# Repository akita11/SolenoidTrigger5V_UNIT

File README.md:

# SolenoidTrigger5V UNIT

5V電源のみで[タカハのスリムロック](https://www.takaha.co.jp/co/product-slim-lock/)など12V程度以上の高い電圧が必要な負荷を、コンデンサに蓄積したエネルギーで短時間駆動できるユニットです。駆動後は、繰り返しエネルギーを充電して駆動することができます。なおスリムロックの開閉状態をGrove端子から計測するための接続端子もあります。

## 使い方（接続方法）

オレンジの端子に、以下のように負荷を接続します。
- スリムロックのソレノイド（白ワイヤ）: 基板裏面"SOL"側（極性なし）
- スリムロックの開閉センサ（赤ワイヤ）: 基板裏面"ST"側（極性なし）

Grove端子にはM5Stack等のマイコンに接続します。

## 使い方（ソフトウエア）

Grove端子のp1（コネクタの端側）を駆動信号TRGを"1"にすると、コンデンサに蓄積したエネルギーでスリムロックなどの負荷を一瞬だけ駆動します（施錠状態のスリムロックが解錠されます）。
なお"1"にしてから負荷が駆動されるまでに0.5秒程度時間がかかります。充電動作中はオレンジLEDが点灯し、その間は負荷の駆動が行われません。

Grove端子のp2（コネクタのVDD側）は、ST端子がショート時には"0"、オープン時には"1"となり、Grove端子に接続したM5Stack等のマイコンから読み取ることができます。（内部プルアップ）

### UIFlow(v1)用のカスタムブロック

UIFlow(v1)で、Customから"SolenoidTrigger5V.m5b"を読み込むと、"SolenoidTrigger5VUnit"内の3つのブロックが使えるようになります。（上図はこれを読み込んだあと、"SolenoidTrgger5VUNIT_test_Core2.m5f"を読み込んだ例）

- Init : 解除信号(Groveのp1端子:CtrlPin)とST端子状態(Groveのp2端子:StatusPin)のピン番号を指定します。最初に1回だけ実行します。例：Core2のPortAはp1=GPIO33、p2=GPIO32なので、この図のように指定します。その他の機種・ポートのピン番号は仕様を確認してください。
- Unlock : ロック解除を行います
- Status : ST端子の状態を取得します。スリムロックの場合は、解錠時に"1"、施錠時に"0"になります。

## Author

Junichi Akita (@akita11) / akita@ifdl.jp

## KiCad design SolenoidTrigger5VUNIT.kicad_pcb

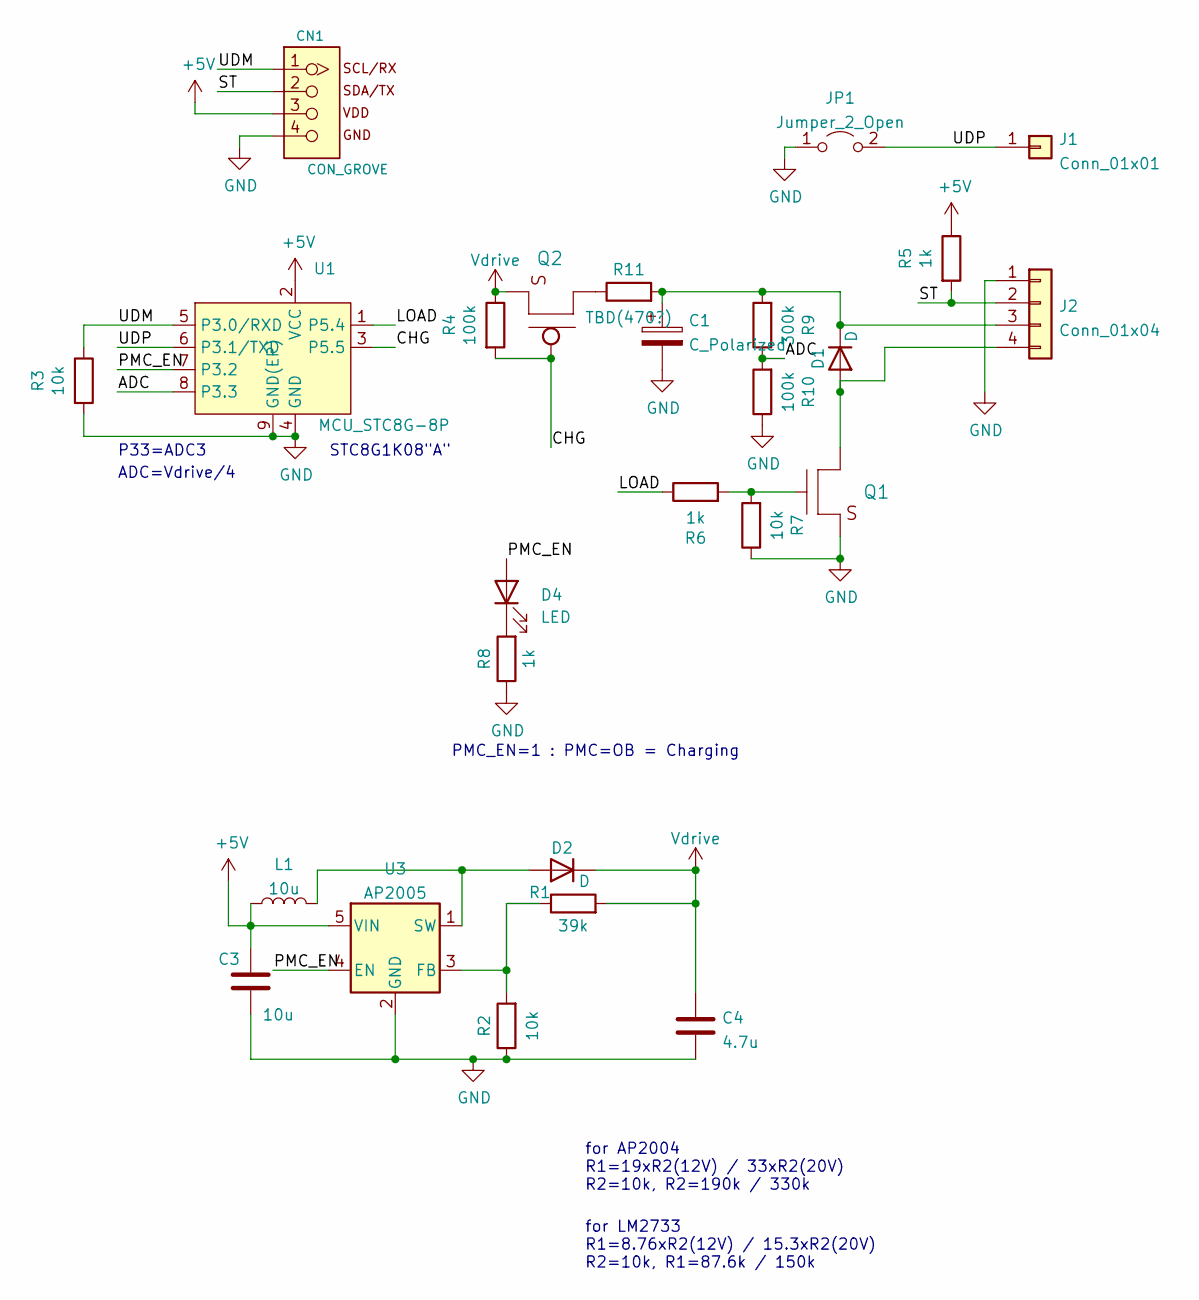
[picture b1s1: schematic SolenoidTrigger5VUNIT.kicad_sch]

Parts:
C1: C_Polarized; CP_Radial_D8.0mm_P3.50mm
C3: 10u; C_0603_1608Metric; LCSC C96446
C4: 4.7u; C_0603_1608Metric; LCSC C96446
CN1: CON_GROVE; CON_GROVE_H
D1, D2: D; D_SOD-123F; LCSC C2760867
D4: LED; LED_0603_1608Metric; LCSC C165982
J1: Conn_01x01; 1p_TH
J2: Conn_01x04; JST_VH_B4PS-VH_1x04_P3.96mm_Horizontal
JP1: Jumper_2_Open; SolderJumper-2_P1.3mm_Open_Pad1.0x1.5mm
L1: 10u; L_CD43; LCSC C5159664
Q1: TR_NMOS_IRLML6344; SOT-23; LCSC C20917
Q2: TR_PMOS_IRLML6402; SOT-23
R1: 39k; R_0603_1608Metric; LCSC C2907160
R2: 10k; R_0603_1608Metric; LCSC C25804
R3, R7: 10k; R_0603_1608Metric; LCSC C21190
R4, R10: 100k; R_0603_1608Metric; LCSC C21190
R5, R6, R8: 1k; R_0603_1608Metric; LCSC C21190
R9: 300k; R_0603_1608Metric; LCSC C21190
R11: TBD(470?); R_0603_1608Metric; LCSC C21190
U1: MCU_STC8G-8P; DFN-8-1EP_3x3mm_P0.5mm_EP1.65x2.38mm; LCSC C915664
U3: AP2005; SOT-23-6; LCSC C130339

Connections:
+5V: C3.1, CN1.3, L1.1, R5.1, U1.2 (VCC), U3.5 (VIN)
/ADC: R9.1, R10.2, U1.8 (P3.3)
/CHG: Q2.1 (G), R4.2, U1.3 (P5.5)
/LOAD: R6.1, U1.1 (P5.4)
/PMC_EN: D4.2 (A), U1.7 (P3.2), U3.4 (EN)
/ST: CN1.2, J2.2, R5.2
/UDM: CN1.1, R3.1, U1.5 (P3.0/RXD)
/UDP: J1.1, JP1.2 (B), U1.6 (P3.1/TXD)
GND: C1.2, C3.2, C4.2, CN1.4, J2.1, JP1.1 (A), Q1.2 (S), R2.1, R3.2, R7.1, R8.1, R10.1, U1.4 (GND), U1.9 (GND(EP)), U3.2 (GND)
unnamed: C1.1, D1.1 (K), J2.3, R9.2, R11.2
unnamed: D1.2 (A), J2.4, Q1.3 (D)
unnamed: D2.2 (A), L1.2, U3.1 (SW)
unnamed: D4.1 (K), R8.2
unnamed: Q1.1 (G), R6.2, R7.2
unnamed: Q2.3 (D), R11.1
unnamed: R1.1, R2.2, U3.3 (FB)
Vdrive: C4.1, D2.1 (K), Q2.2 (S), R1.2, R4.1

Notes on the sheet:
STC8G1K08"A"
ADC=Vdrive/4
for LM2733 R1=8.76xR2(12V) / 15.3xR2(20V) R2=10k, R1=87.6k / 150k
P33=ADC3
for AP2004 R1=19xR2(12V) / 33xR2(20V) R2=10k, R2=190k / 330k
PMC_EN=1 : PMC=OB = Charging

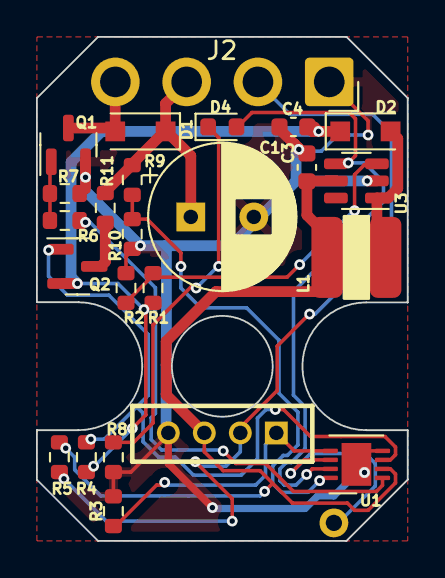
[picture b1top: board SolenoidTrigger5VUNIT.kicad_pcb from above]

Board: 2 copper layers, 20.6 x 28.0 mm, 26 parts (1 on the bottom side), 17 nets.

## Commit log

2025-01-18 add photo
2025-01-18 photo name typo fix
2025-01-30 update photo
2025-01-30 add FW source code
2025-03-15 add custom block
